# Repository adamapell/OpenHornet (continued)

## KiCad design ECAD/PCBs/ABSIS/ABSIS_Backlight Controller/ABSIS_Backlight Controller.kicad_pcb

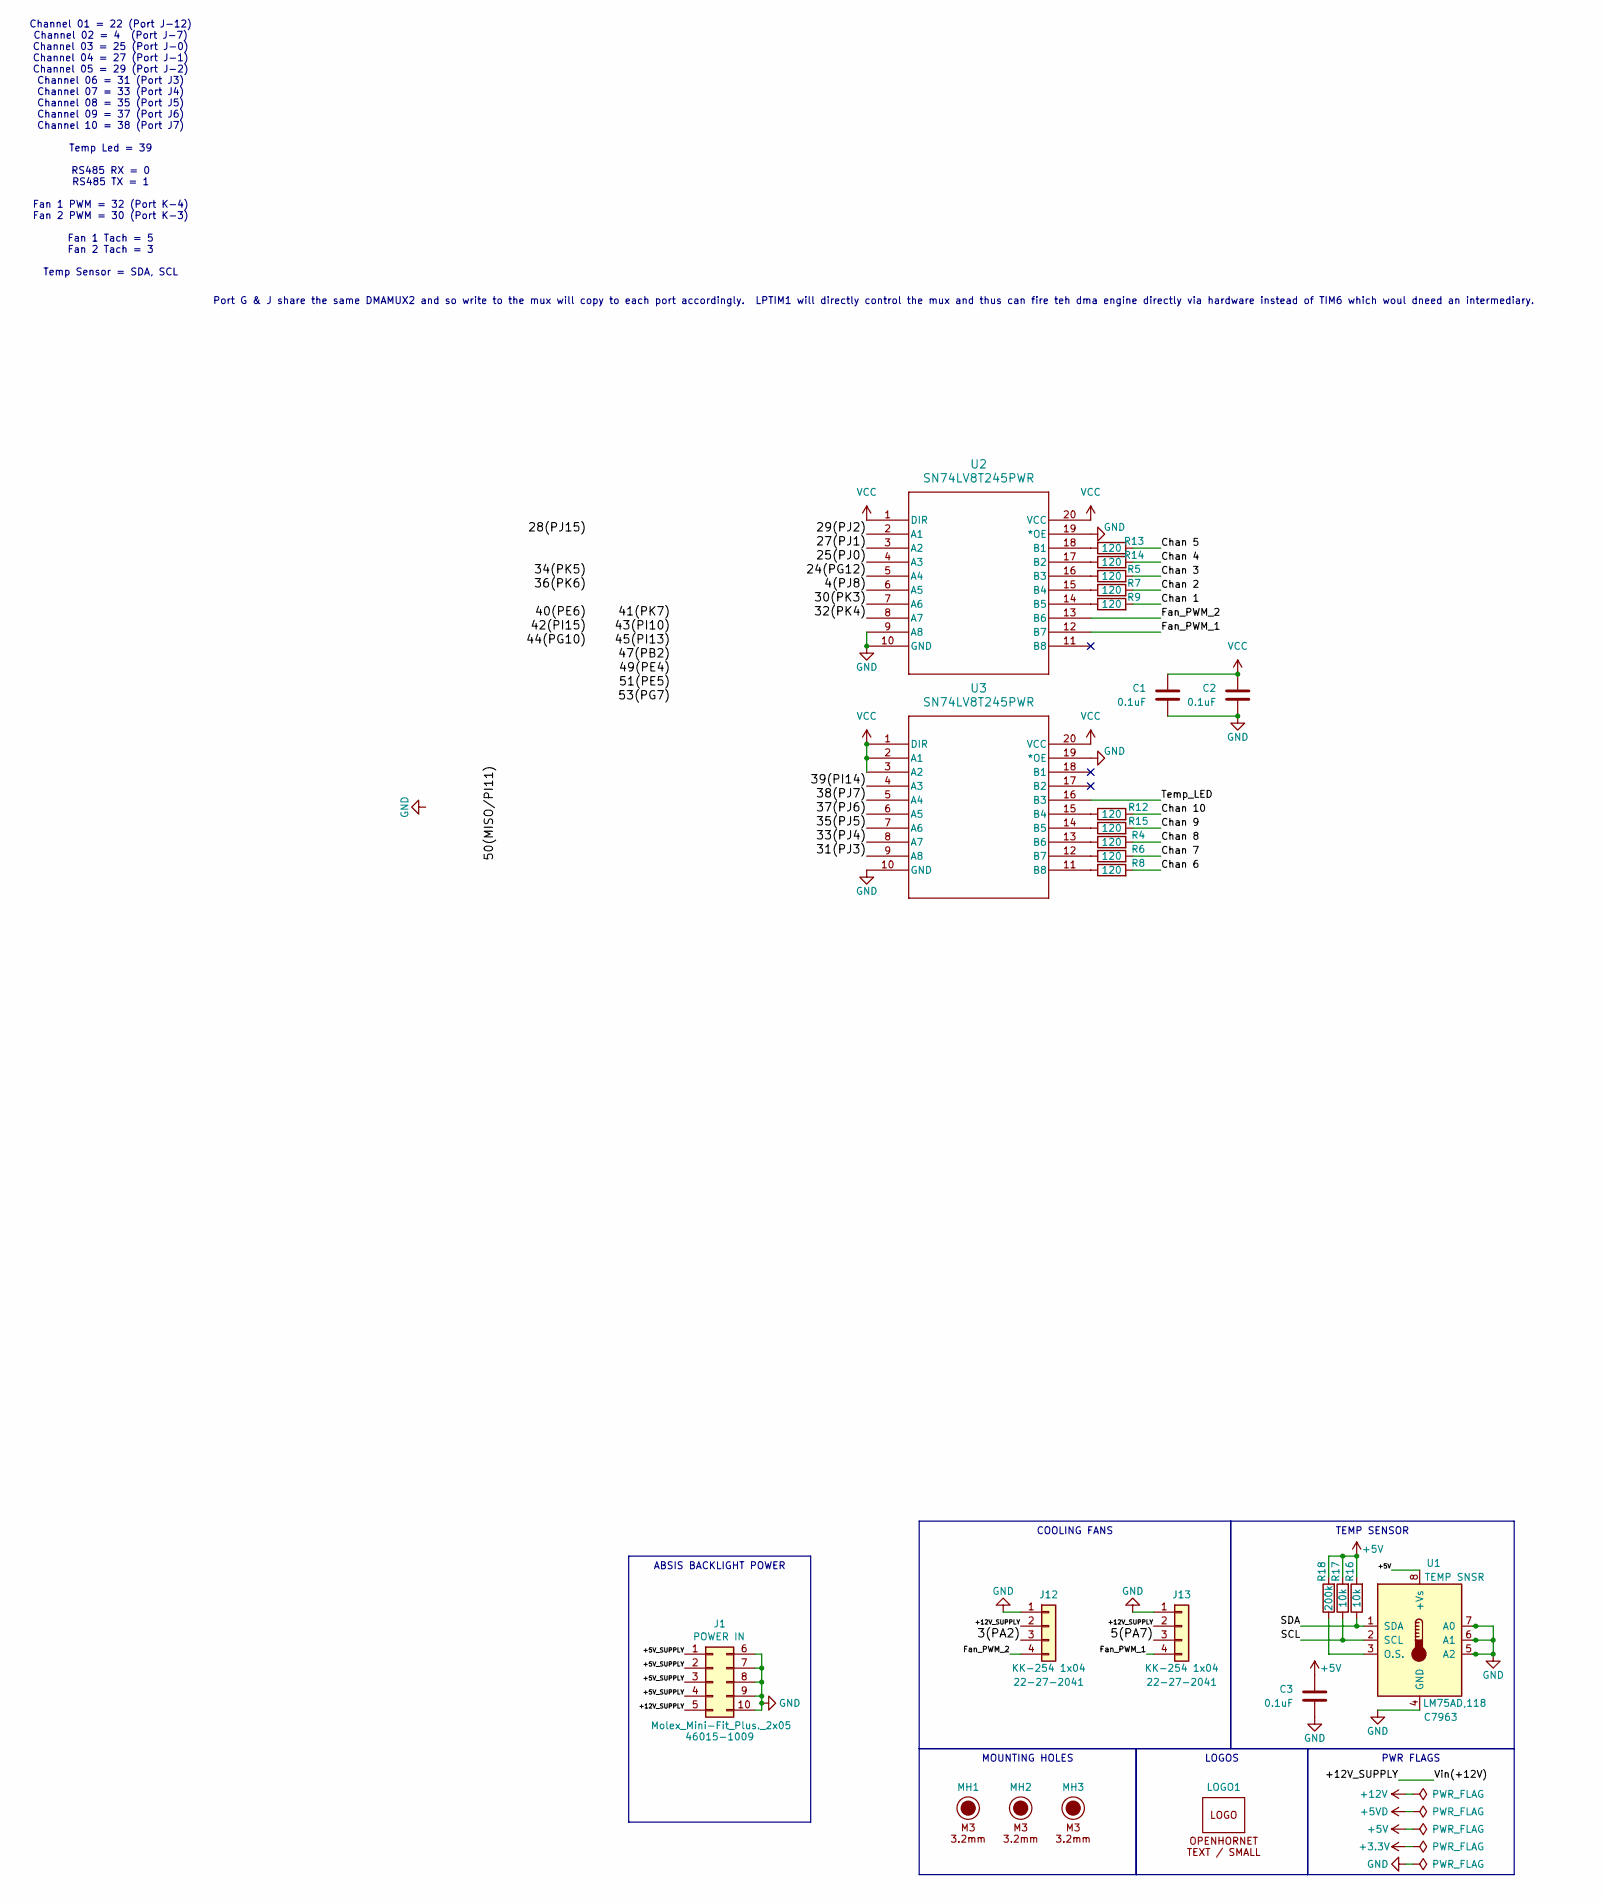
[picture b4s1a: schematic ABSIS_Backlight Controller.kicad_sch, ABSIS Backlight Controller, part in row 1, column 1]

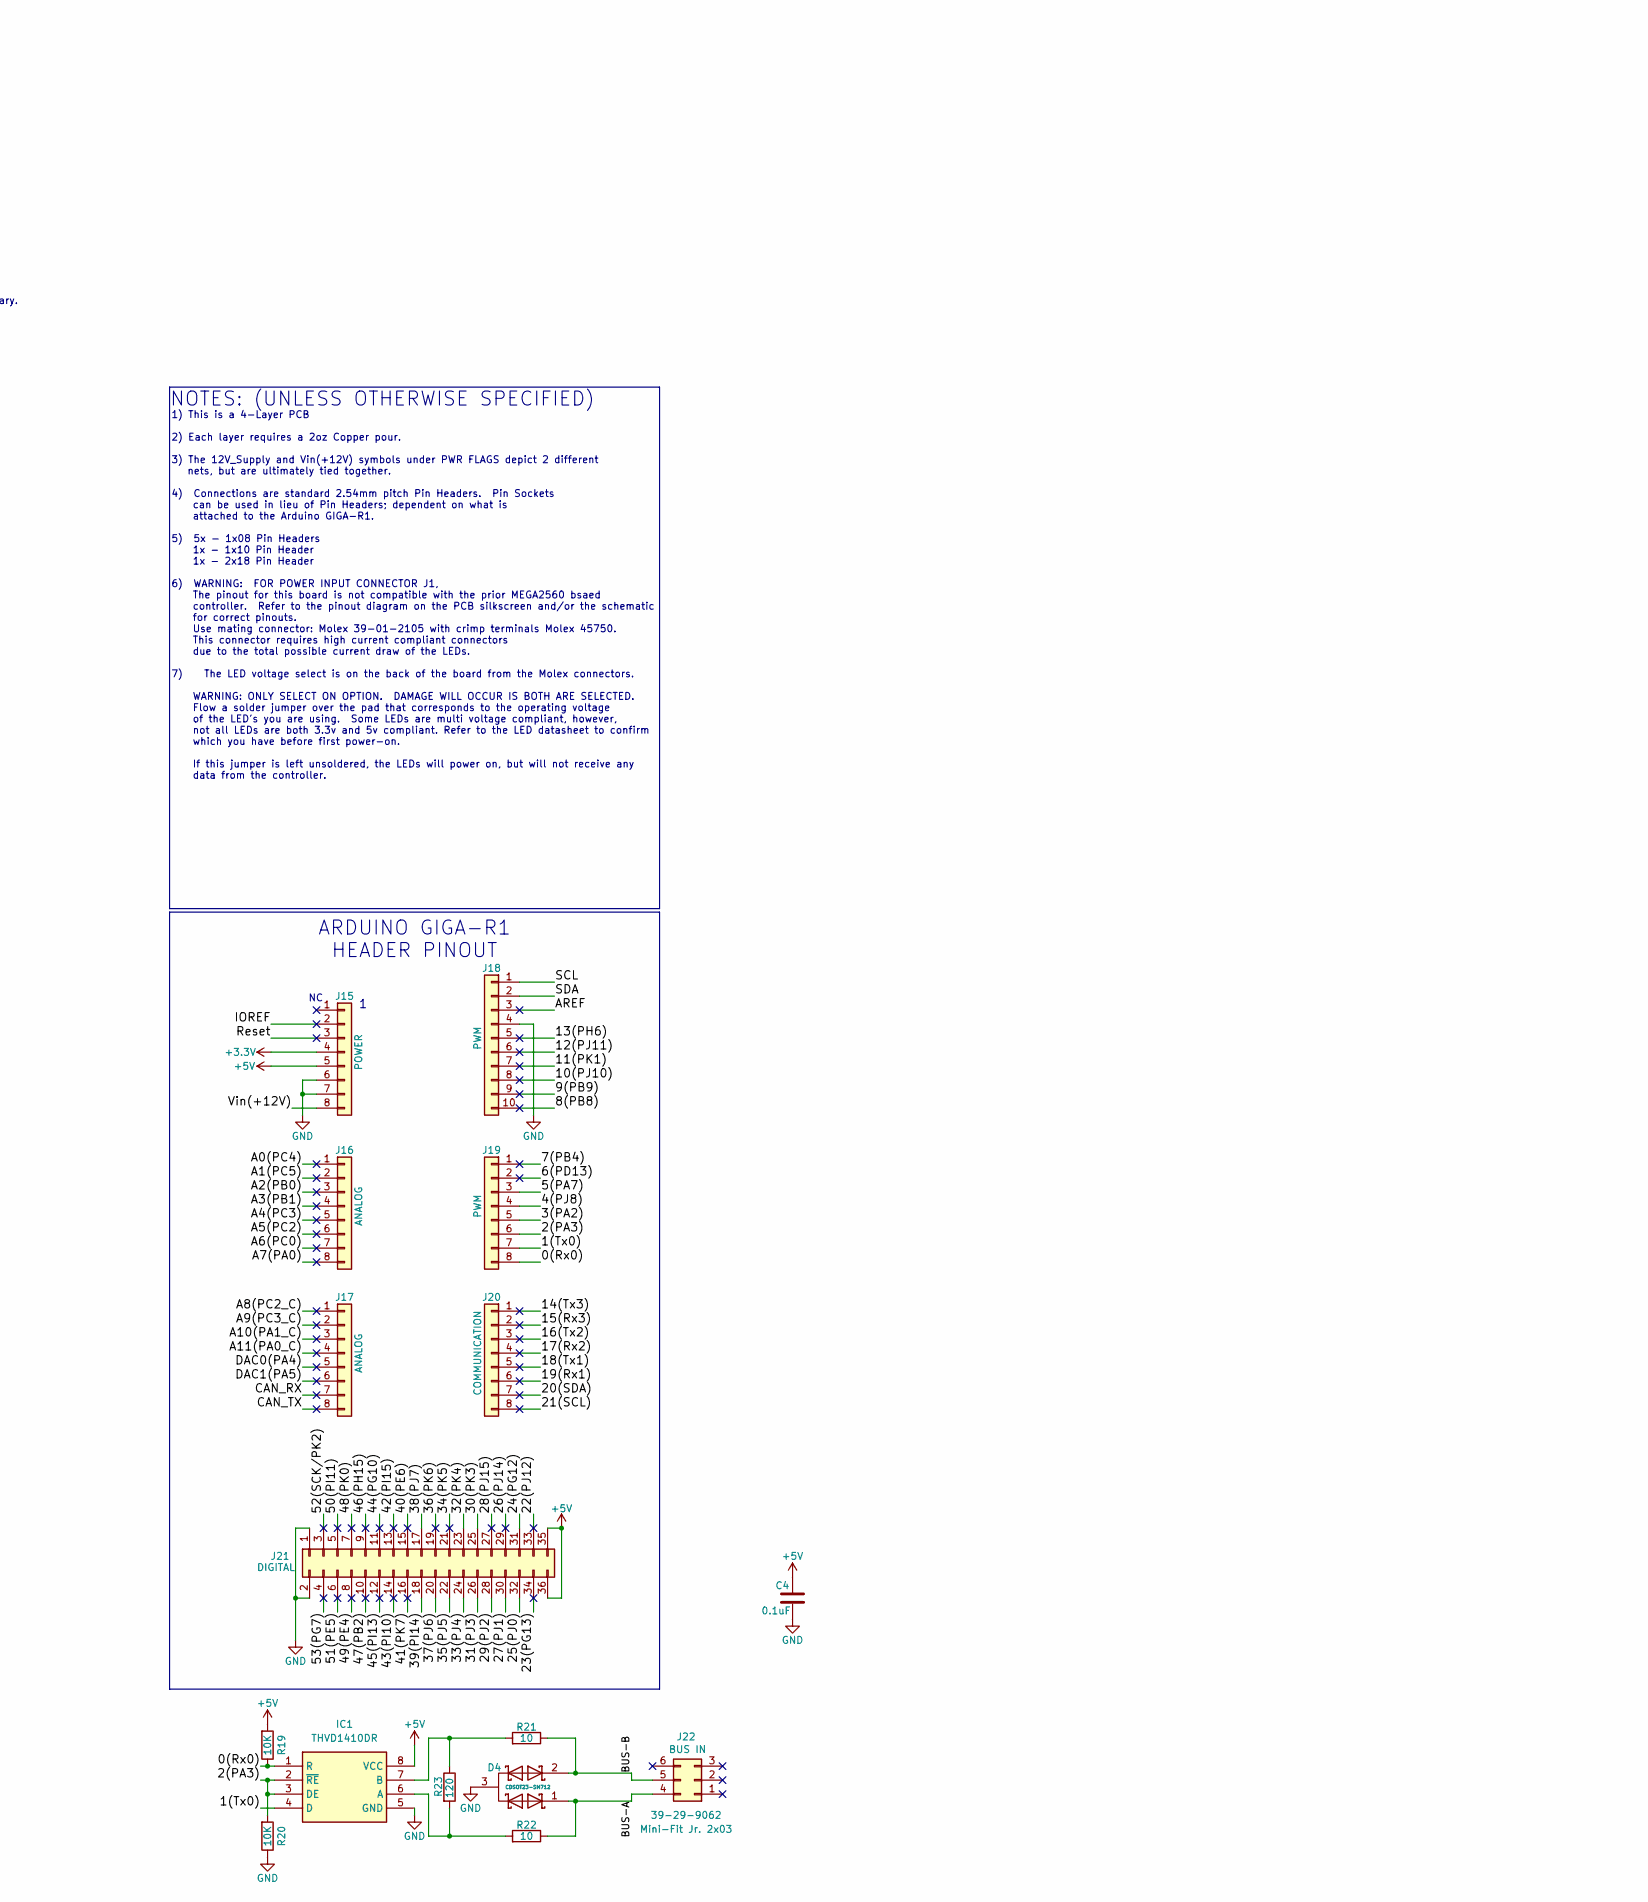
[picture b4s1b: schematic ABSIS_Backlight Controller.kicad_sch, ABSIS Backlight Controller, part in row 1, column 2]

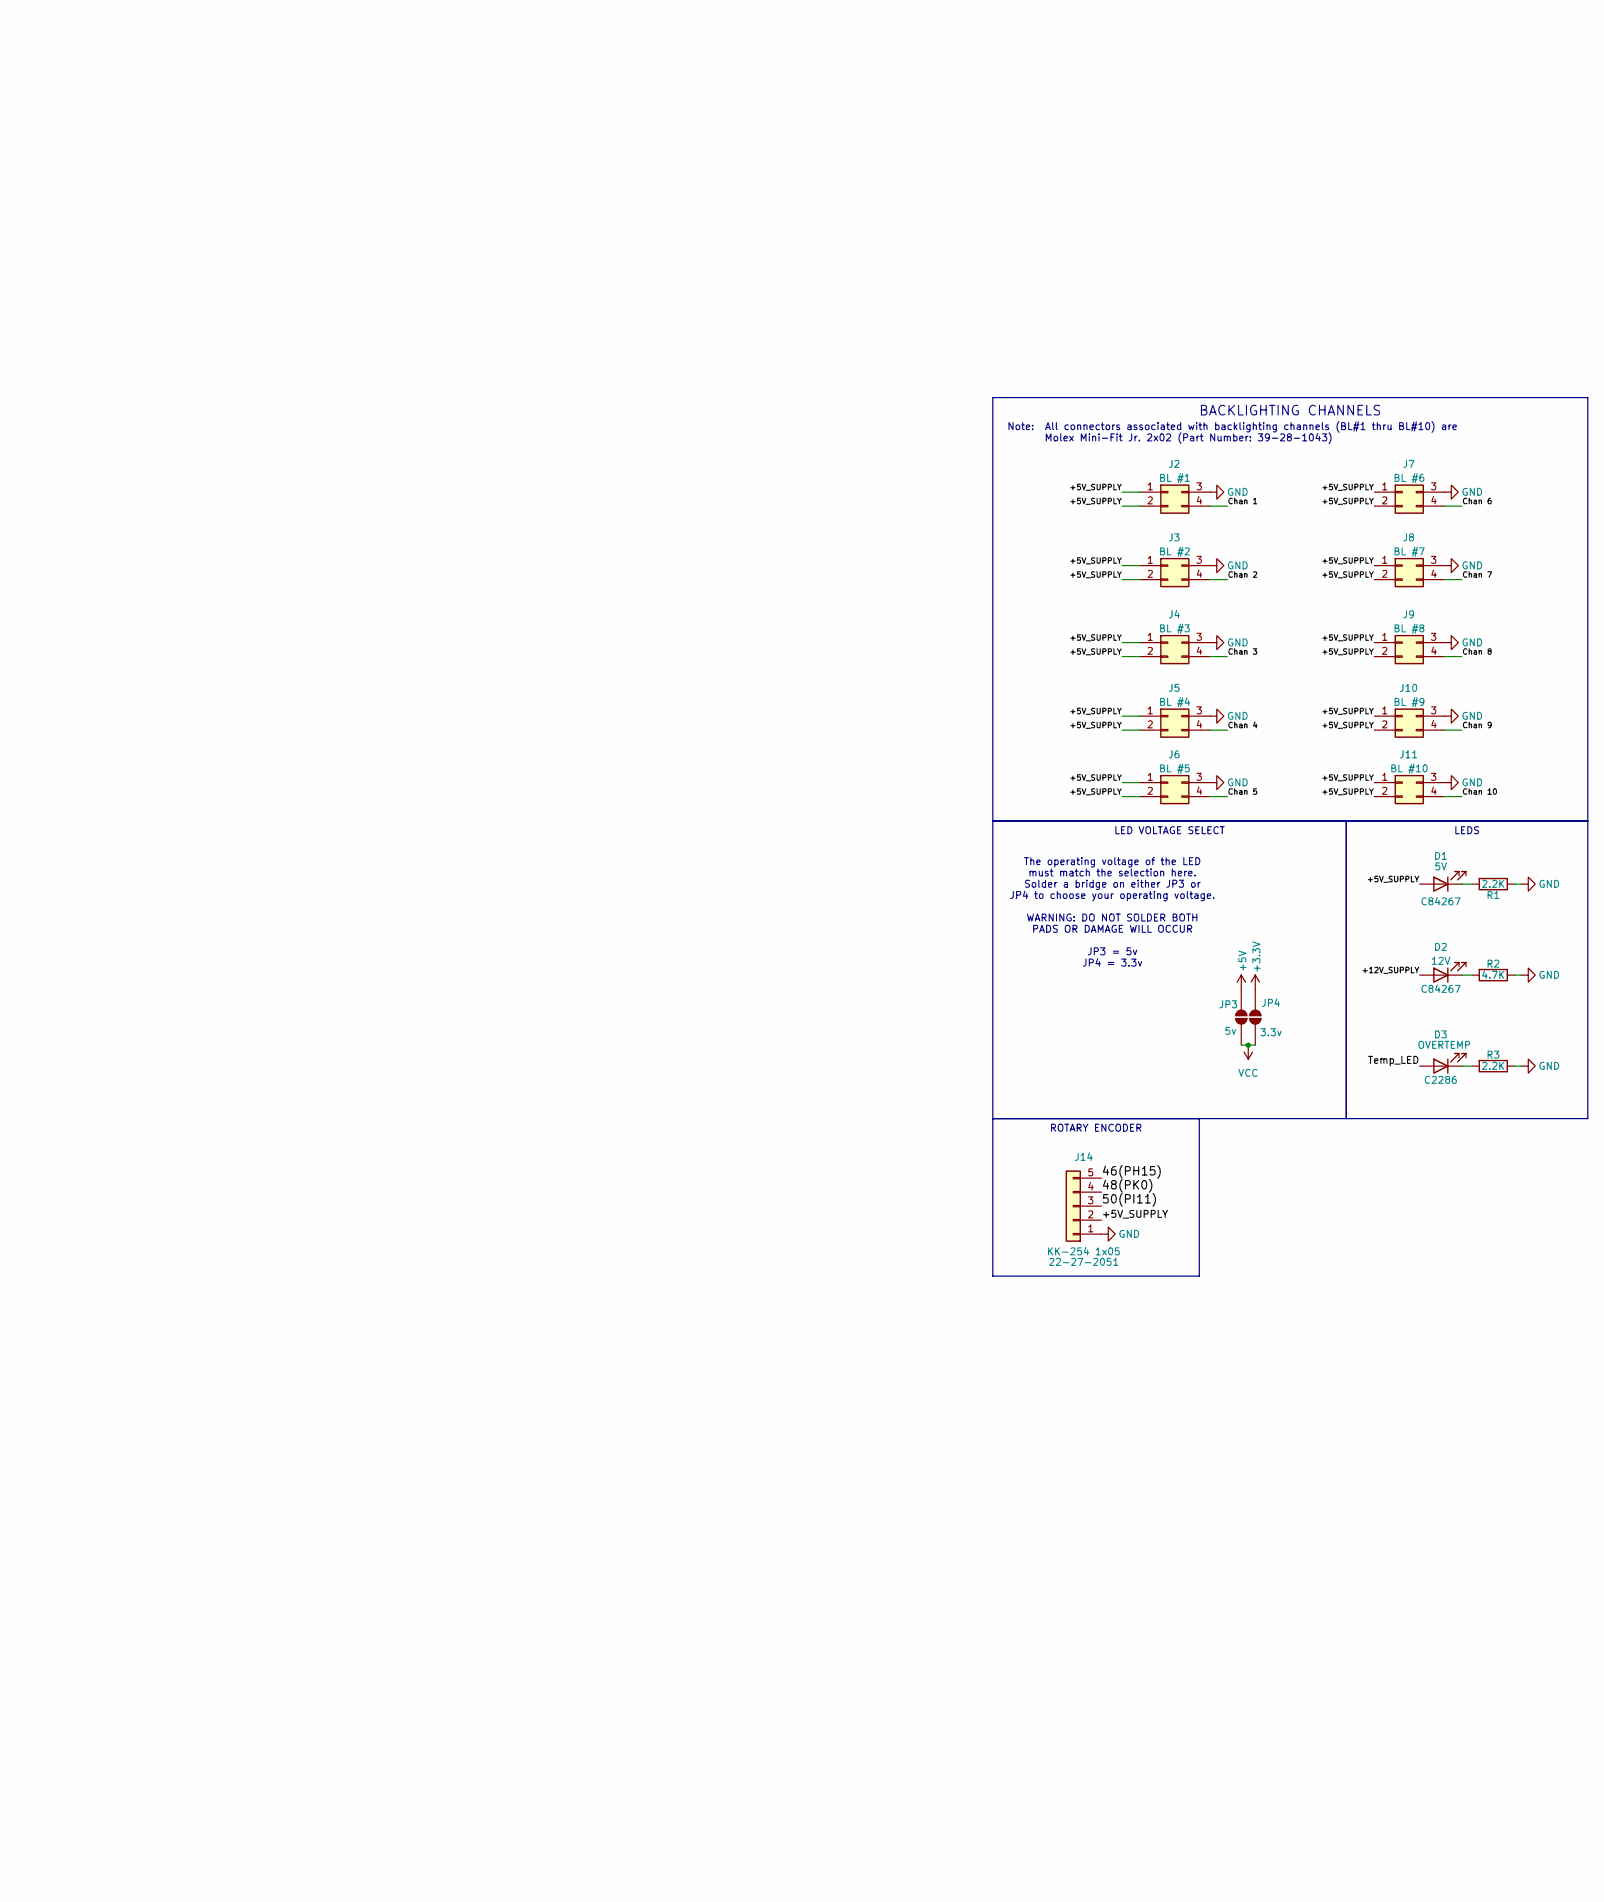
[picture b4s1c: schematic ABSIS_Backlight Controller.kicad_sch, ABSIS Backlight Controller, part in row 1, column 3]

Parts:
C1, C2, C3, C4: 0.1uF; C_0603_1608Metric; Manufacturer PN CC0603KRX7R9BB104; LCSC C14663
D1, D2: Green; LED_0603_1608Metric_Pad1.05x0.95mm_HandSolder; Manufacturer PN NCD0603G1; LCSC C84267
D3: Red; LED_0603_1608Metric_Pad1.05x0.95mm_HandSolder; Manufacturer PN KT-0603R; LCSC C2286
D4: CDSOT23-SM712; Manufacturer_Part_Number CDSOT23-SM712; Mouser Part Number 652-CDSOT23-SM712
IC1: THVD1410DR; Manufacturer_Part_Number THVD1410DR; Mouser Part Number 595-THVD1410DR
J1: Molex_Mini-Fit_Plus._2x05; Molex_Mini-Fit_Jr_5566-10A2_2x05_P4.20mm_Vertical; Manufacturer PN 46015-1009; LCSC C587474
J2, J3, J4, J5, J6, J7, J8, J9, J10, J11: Mini-Fit Jr. 2x02; Molex_Mini-Fit_Jr_5566-04A_2x02_P4.20mm_Vertical; Manufacturer PN 39-28-1043; LCSC C293502
J12, J13: KK-254 1x04; Molex_KK-254_AE-6410-04A_1x04_P2.54mm_Vertical; Manufacturer PN 22-27-2041; LCSC C504991
J14: KK-254 1x05; Molex_KK-254_AE-6410-05A_1x05_P2.54mm_Vertical; Manufacturer PN 22-27-2051; LCSC C585785
J15, J16, J17, J19, J20: PinHeader_1x08; PinHeader_1x08_P2.54mm_Vertical; Manufacturer PN PH1-08-UA
J18: PinHeader_1x10; PinHeader_1x10_P2.54mm_Vertical; Manufacturer PN PH1-10-UA
J21: PinHeader_2x18; PinHeader_2x18_P2.54mm_Vertical; Manufacturer PN PH2-18-UA
J22: Mini-Fit Jr. 2x03; Molex_Mini-Fit_Jr_5566-06A2_2x03_P4.20mm_Vertical; Manufacturer PN 39-29-9062; LCSC C505177
JP3: 5v; SolderJumper-2_P1.3mm_Open_RoundedPad1.0x1.5mm
JP4: 3.3v; SolderJumper-2_P1.3mm_Open_RoundedPad1.0x1.5mm
LOGO1: LOGO; LOGO_OH_Text_Small
MH1, MH2, MH3: M3 / 3.2mm; MountingHole_3.2mm_M3_DIN965
R1, R3: 2.2K; R_0603_1608Metric; Manufacturer PN 0603WAF2201T5E; LCSC C4190
R2: 4.7K; R_0603_1608Metric; Manufacturer PN 0603WAF4701T5E; LCSC C23162
R4, R5, R6, R7, R8, R9, R12, R13, R14, R15, R23: 120; R_0603_1608Metric; Manufacturer PN 0603WAF1200T5E; LCSC C22787
R16, R17: 10k; R_0603_1608Metric; Manufacturer PN 0603WAF1002T5E; LCSC C25804
R18: 200k; R_0603_1608Metric; Manufacturer PN 0603WAF2201T5E; LCSC C25811
R19, R20: 10K; R_0603_1608Metric_Pad0.98x0.95mm_HandSolder; LCSC C25804
R21, R22: 10; R_0603_1608Metric_Pad0.98x0.95mm_HandSolder; LCSC C844519
U1: LM75AD,118; SOIC-8_3.9x4.9mm_P1.27mm; Manufacturer PN LM75AD,118; LCSC C7963
U2, U3: SN74LV8T245PWR; TSSOP20_PW_TEX; LCSC C20345798

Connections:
+3.3V: J15.4, JP4.2 (B)
+5V: C3.1, C4.2, IC1.8 (VCC), J15.5, J21.35, J21.36, JP3.2 (B), R16.2, R17.2, R18.2, R19.2, U1.8 (+Vs)
/0(Rx0): IC1.1 (R), J19.8, R19.1
/1(Tx0): IC1.4 (D), J19.7
/2(PA3): IC1.2 (~RE), IC1.3 (DE), J19.6, R20.2
/3(PA2): J12.3, J19.5
/4(PJ8): J19.4, U2.6 (A5)
/5(PA7): J13.3, J19.3
/6(PD13): J19.2
/7(PB4): J19.1
/8(PB8): J18.10
/9(PB9): J18.9
/10(PJ10): J18.8
/11(PK1): J18.7
/12(PJ11): J18.6
/13(PH6): J18.5
/14(Tx3): J20.1
/15(Rx3): J20.2
/16(Tx2): J20.3
/17(Rx2): J20.4
/18(Tx1): J20.5
/19(Rx1): J20.6
/20(SDA): J20.7
/21(SCL): J20.8
/22(PJ12): J21.33
/23(PG13): J21.34
/24(PG12): J21.31, U2.5 (A4)
/25(PJ0): J21.32, U2.4 (A3)
/26(PJ14): J21.29
/27(PJ1): J21.30, U2.3 (A2)
/28(PJ15): J21.27
/29(PJ2): J21.28, U2.2 (A1)
/30(PK3): J21.25, U2.7 (A6)
/31(PJ3): J21.26, U3.9 (A8)
/32(PK4): J21.23, U2.8 (A7)
/33(PJ4): J21.24, U3.8 (A7)
/34(PK5): J21.21
/35(PJ5): J21.22, U3.7 (A6)
/36(PK6): J21.19
/37(PJ6): J21.20, U3.6 (A5)
/38(PJ7): J21.17, U3.5 (A4)
/39(PI14): J21.18, U3.4 (A3)
/40(PE6): J21.15
/41(PK7): J21.16
/42(PI15): J21.13
/43(PI10): J21.14
/44(PG10): J21.11
/45(PI13): J21.12
/46(PH15): J14.5, J21.9
/47(PB2): J21.10
/48(PK0): J14.4, J21.7
/49(PE4): J21.8
/50(PI11): J14.3, J21.5
/51(PE5): J21.6
/52(SCK/PK2): J21.3
/53(PG7): J21.4
/+5V_SUPPLY: D1.2 (A), J1.1, J1.2, J1.3, J1.4, J2.1, J2.2 (Pin_3), J3.1, J3.2 (Pin_3), J4.1, J4.2 (Pin_3), J5.1, J5.2 (Pin_3), J6.1, J6.2 (Pin_3), J7.1, J7.2 (Pin_3), J8.1, J8.2 (Pin_3), J9.1, J9.2 (Pin_3), J10.1, J10.2 (Pin_3), J11.1, J11.2 (Pin_3), J14.2
/+12V_SUPPLY: D2.2 (A), J1.5, J12.2, J13.2, J15.8
/A0(PC4): J16.1
/A1(PC5): J16.2
/A2(PB0): J16.3
/A3(PB1): J16.4
/A4(PC3): J16.5
/A5(PC2): J16.6
/A6(PC0): J16.7
/A7(PA0): J16.8
/A8(PC2_C): J17.1
/A9(PC3_C): J17.2
/A10(PA1_C): J17.3
/A11(PA0_C): J17.4
/AREF: J18.3
/BUS-A: D4.1, J22.4, R22.2
/BUS-B: D4.2, J22.5, R21.2
/CAN_RX: J17.7
/CAN_TX: J17.8
/Chan 1: J2.4, R9.2
/Chan 2: J3.4, R7.2
/Chan 3: J4.4, R5.2
/Chan 4: J5.4, R14.2
/Chan 5: J6.4, R13.2
/Chan 6: J7.4, R8.2
/Chan 7: J8.4, R6.2
/Chan 8: J9.4, R4.2
/Chan 9: J10.4, R15.2
/Chan 10: J11.4, R12.2
/DAC0(PA4): J17.5
/DAC1(PA5): J17.6
/Fan_PWM_1: J13.4, U2.12 (B7)
/Fan_PWM_2: J12.4, U2.13 (B6)
/IOREF: J15.2
/Reset: J15.3
/SCL: J18.1, R17.1, U1.2 (SCL)
/SDA: J18.2, R16.1, U1.1 (SDA)
/Temp_LED: D3.2 (A), U3.16 (B3)
GND: C1.2, C2.2, C3.2, C4.1, D4.3, IC1.5 (GND), J1.6, J1.7, J1.8, J1.9, J1.10, J2.3 (Pin_2), J3.3 (Pin_2), J4.3 (Pin_2), J5.3 (Pin_2), J6.3 (Pin_2), J7.3 (Pin_2), J8.3 (Pin_2), J9.3 (Pin_2), J10.3 (Pin_2), J11.3 (Pin_2), J12.1, J13.1, J14.1, J15.6, J15.7, J18.4, J21.1, J21.2, R1.1, R2.1, R3.1, R20.1, U1.4 (GND), U1.5 (A2), U1.6 (A1), U1.7 (A0), U2.9 (A8), U2.10 (GND), U2.19 (*OE), U3.10 (GND), U3.19 (*OE)
unnamed: D1.1 (K), R1.2
unnamed: D2.1 (K), R2.2
unnamed: D3.1 (K), R3.2
unnamed: IC1.6 (A), R22.1, R23.1
unnamed: IC1.7 (B), R21.1, R23.2
unnamed: R18.1, U1.3 (O.S.)
unnamed: R13.1, U2.18 (B1)
unnamed: R14.1, U2.17 (B2)
unnamed: R5.1, U2.16 (B3)
unnamed: R7.1, U2.15 (B4)
unnamed: R9.1, U2.14 (B5)
unnamed: R12.1, U3.15 (B4)
unnamed: R15.1, U3.14 (B5)
unnamed: R4.1, U3.13 (B6)
unnamed: R6.1, U3.12 (B7)
unnamed: R8.1, U3.11 (B8)
VCC: C1.1, C2.1, JP3.1 (A), JP4.1 (A), U2.1 (DIR), U2.20 (VCC), U3.1 (DIR), U3.2 (A1), U3.3 (A2), U3.20 (VCC)

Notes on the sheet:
The operating voltage of the LED must match the selection here. Solder a bridge on either JP3 or JP4 to choose your operating voltage. WARNING: DO NOT SOLDER BOTH PADS OR DAMAGE WILL OCCUR JP3 = 5v JP4 = 3.3v
1) This is a 4-Layer PCB 2) Each layer requires a 2oz Copper pour. 3) The 12V_Supply and Vin(+12V) symbols under PWR FLAGS depict 2 different nets, but are ultimately tied together. 4) Connections are standard 2.54mm pitch Pin Headers. Pin Sockets can be used in lieu of Pin Headers; dependent on wh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
Port G & J share the same DMAMUX2 and so write to the mux will copy to each port accordingly. LPTIM1 will directly control the mux and thus can fire teh dma engine directly via hardware instead of TIM6 which woul dneed an intermediary.
Note: All connectors associated with backlighting channels (BL#1 thru BL#10) are Molex Mini-Fit Jr. 2x02 (Part Number: 39-28-1043)
Channel 01 = 22 (Port J-12) Channel 02 = 4 (Port J-7) Channel 03 = 25 (Port J-0) Channel 04 = 27 (Port J-1) Channel 05 = 29 (Port J-2) Channel 06 = 31 (Port J3) Channel 07 = 33 (Port J4) Channel 08 = 35 (Port J5) Channel 09 = 37 (Port J6) Channel 10 = 38 (Port J7) Temp Led = 39 RS485 RX = 0 RS485 T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
NOTES: (UNLESS OTHERWISE SPECIFIED)
LEDS
BACKLIGHTING CHANNELS
ABSIS BACKLIGHT POWER
ROTARY ENCODER
TEMP SENSOR
PWR FLAGS
COOLING FANS
LOGOS
MOUNTING HOLES
ARDUINO GIGA-R1 HEADER PINOUT
LED VOLTAGE SELECT

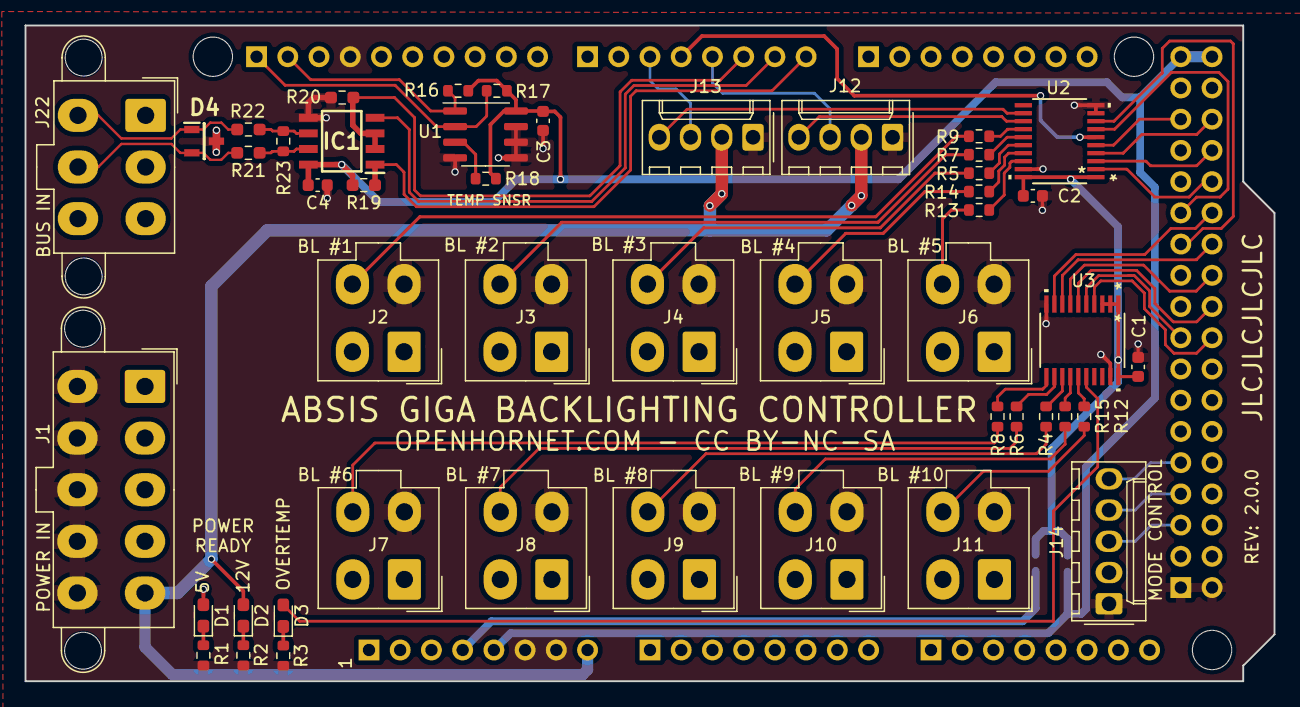
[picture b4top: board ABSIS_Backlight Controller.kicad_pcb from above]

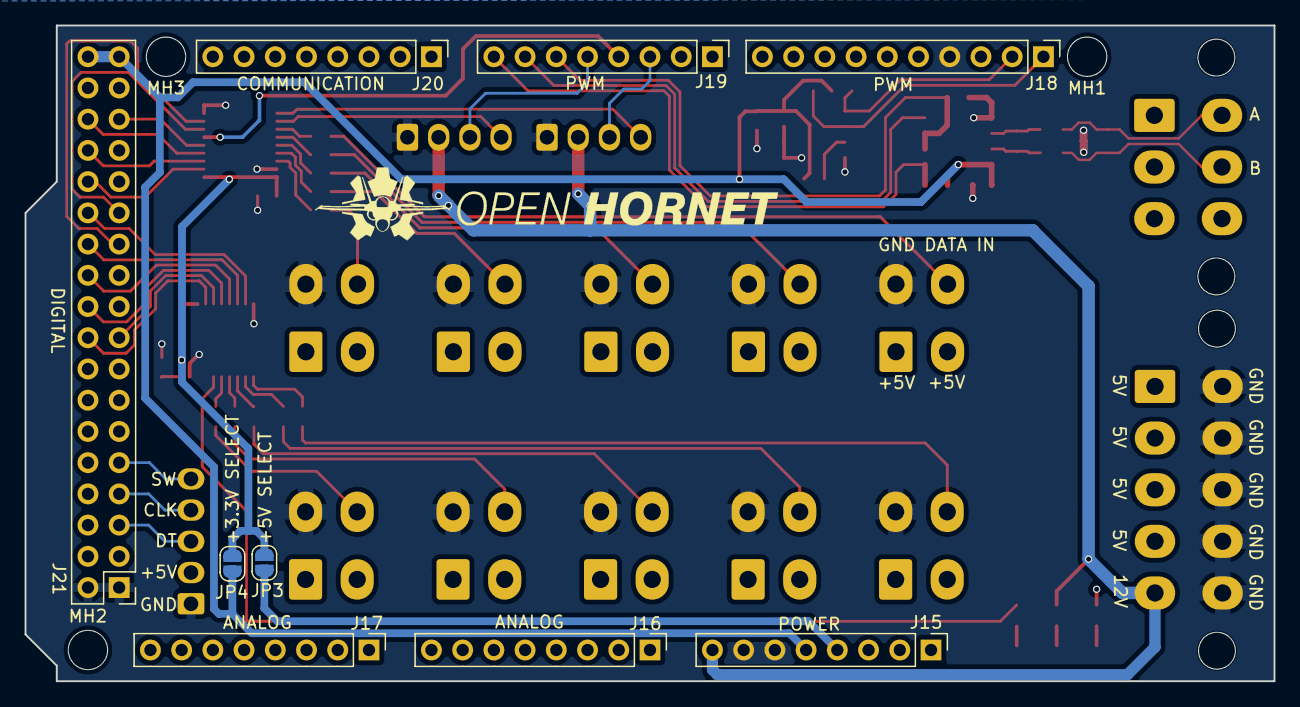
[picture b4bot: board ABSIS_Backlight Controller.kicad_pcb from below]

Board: 4 copper layers, 101.6 x 53.3 mm, 61 parts (13 on the bottom side), 60 nets.

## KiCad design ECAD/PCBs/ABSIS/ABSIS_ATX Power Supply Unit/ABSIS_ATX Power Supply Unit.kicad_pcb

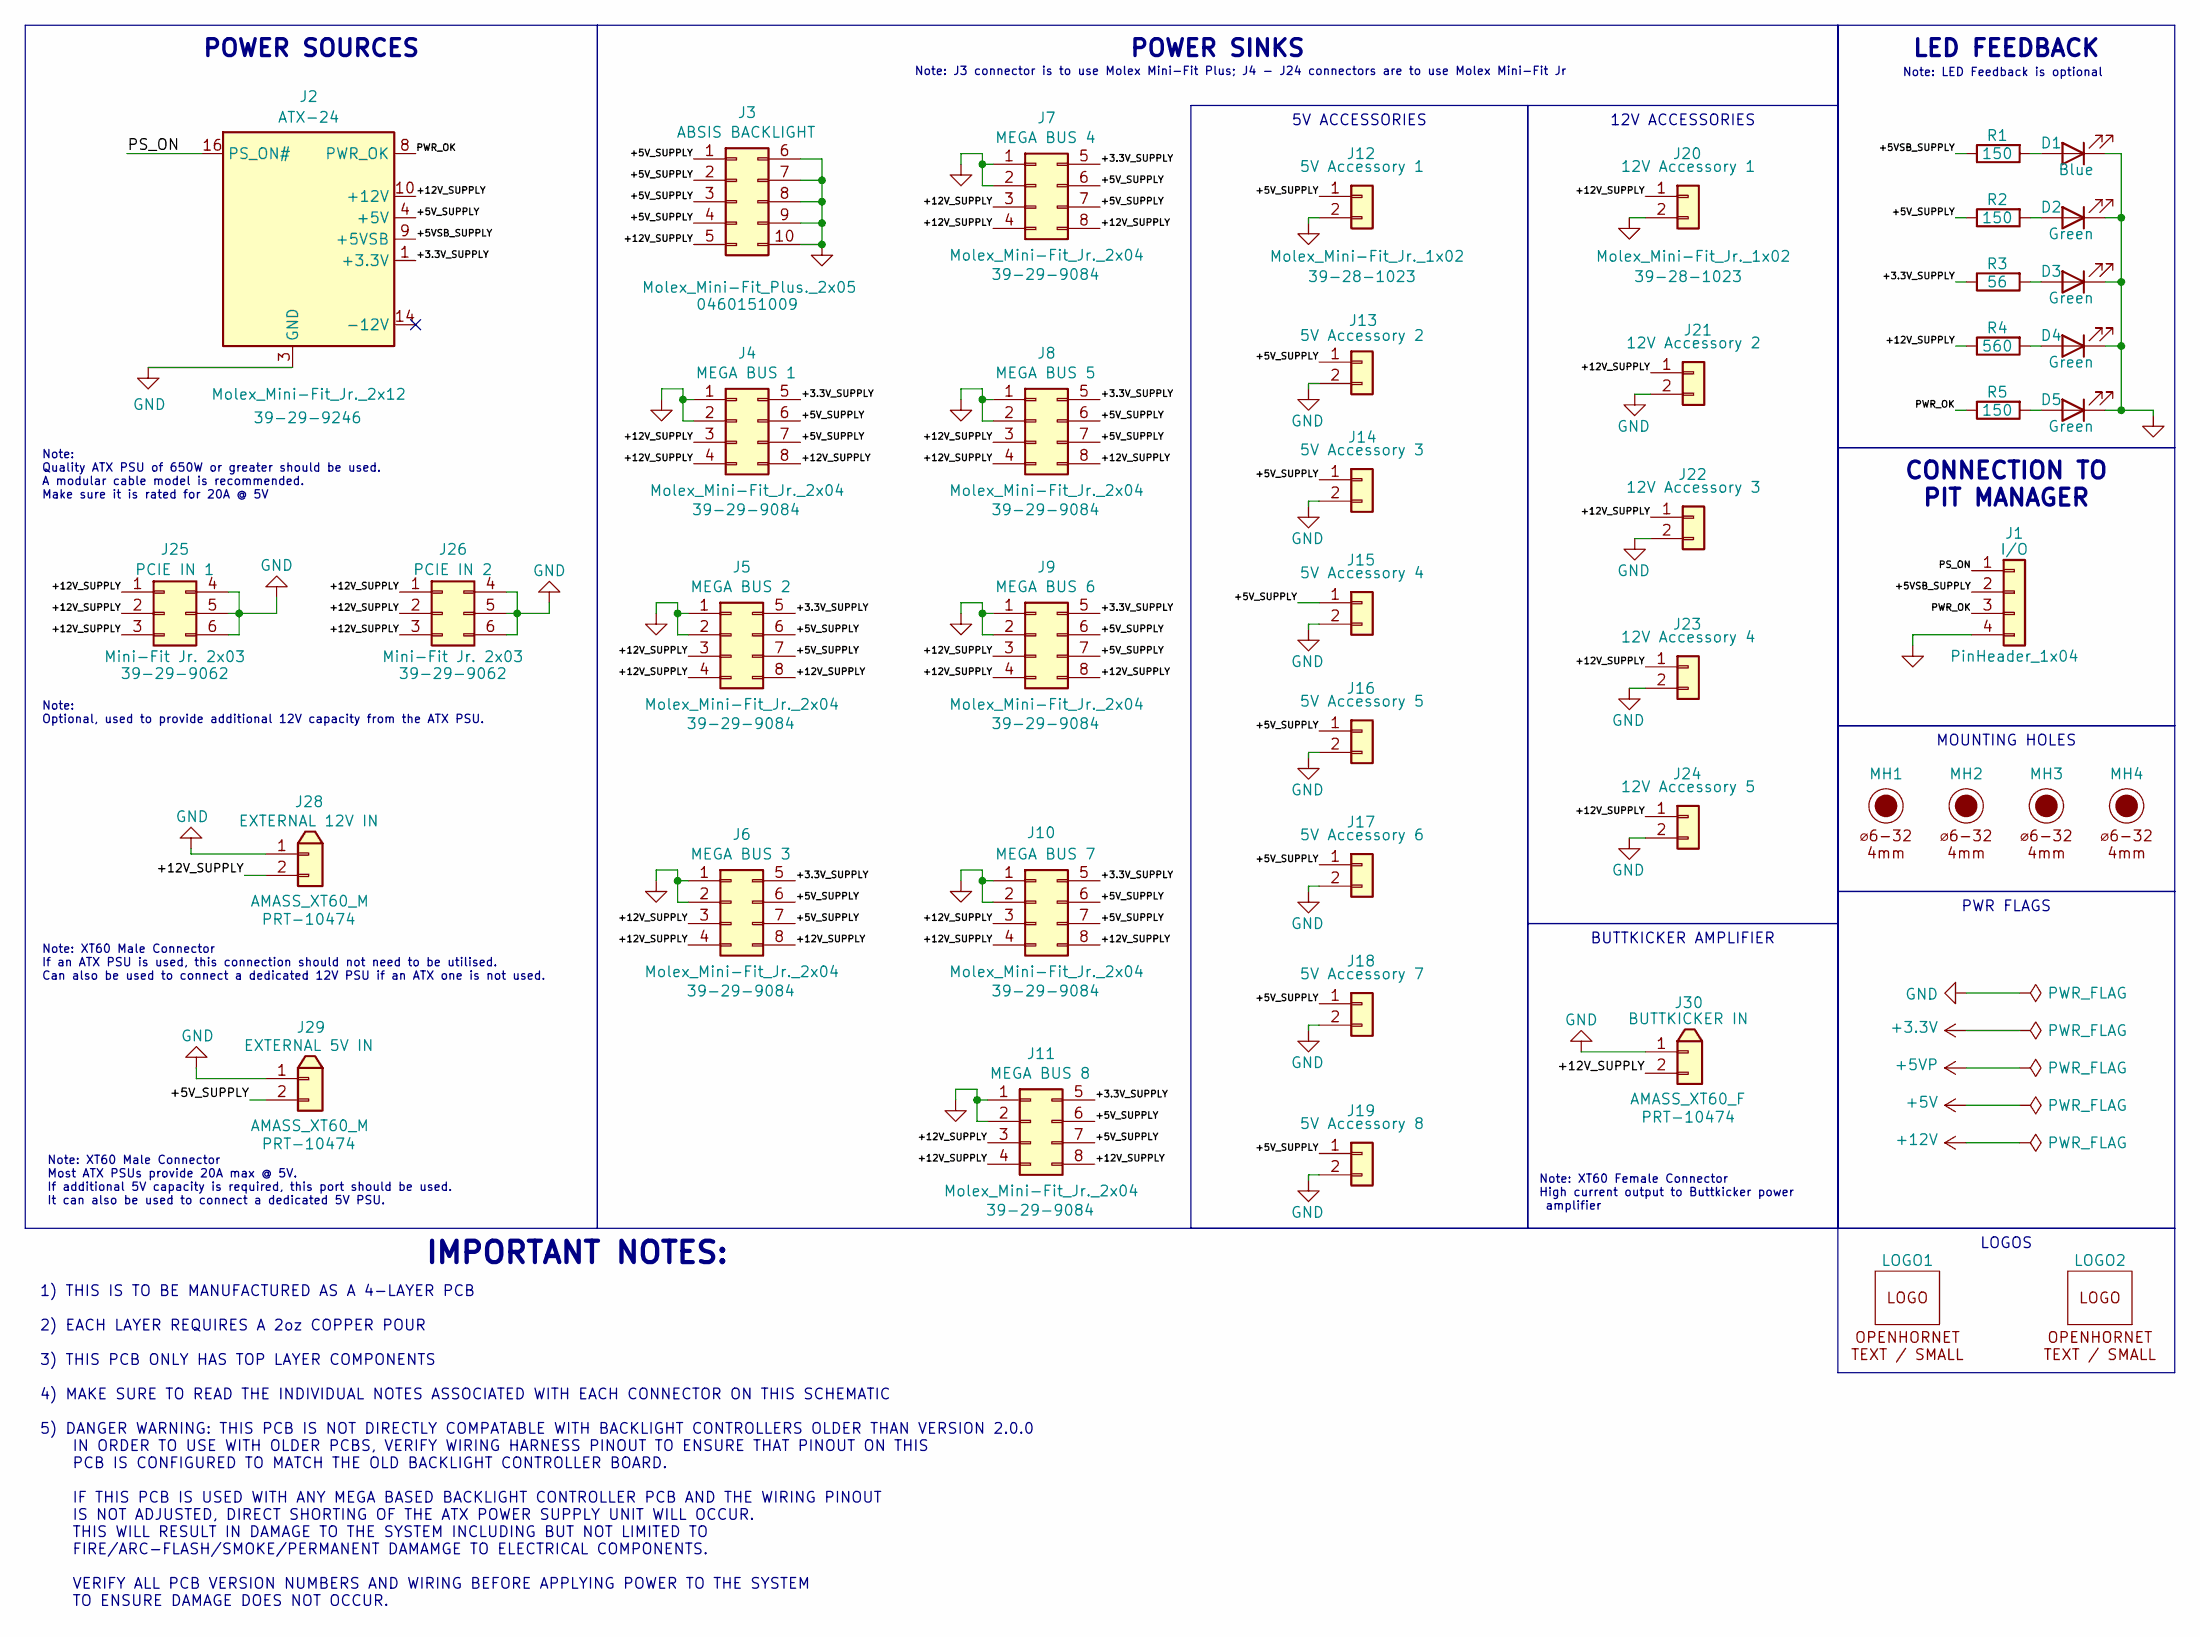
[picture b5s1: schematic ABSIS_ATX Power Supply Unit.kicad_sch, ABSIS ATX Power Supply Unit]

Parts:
D1: Blue; LED_D3.0mm; Manufacturer PN 151033BS03000
D2, D3, D4, D5: Green; LED_D3.0mm; Manufacturer PN 151031VS06000
J1: PinHeader_1x04; PinHeader_1x04_P2.54mm_Vertical
J2: Molex_Mini-Fit_Jr._2x12; Molex_Mini-Fit_Jr_5566-24A2_2x12_P4.20mm_Vertical; Manufacturer PN 39-29-9246; LCSC C587483
J3: Molex_Mini-Fit_Plus._2x05; Molex_Mini-Fit_Jr_5566-10A2_2x05_P4.20mm_Vertical; Manufacturer PN 0460151009; LCSC C17600683
J4, J5, J6, J7, J8, J9, J10, J11: Molex_Mini-Fit_Jr._2x04; Molex_Mini-Fit_Jr_5566-08A2_2x04_P4.20mm_Vertical; Manufacturer PN 39-29-9084; LCSC C587470
J12, J13, J14, J15, J16, J17, J18, J19, J20, J21, J22, J23, J24: Molex_Mini-Fit_Jr._1x02; Molex_Mini-Fit_Jr_5566-02A_2x01_P4.20mm_Vertical; Manufacturer PN 39-28-1023; LCSC C234186
J25, J26: Mini-Fit Jr. 2x03; Molex_Mini-Fit_Jr_5566-06A_2x03_P4.20mm_Vertical; Manufacturer PN 39-29-9062; LCSC C505177
J28, J29: AMASS_XT60_M; AMASS_XT60-M_1x02_P7.20mm_Vertical; Manufacturer PN PRT-10474; LCSC C98733
J30: AMASS_XT60_F; AMASS_XT60-F_1x02_P7.20mm_Vertical; Manufacturer PN PRT-10474; LCSC C98734
LOGO1, LOGO2: LOGO; LOGO_OH_Text_Small
MH1, MH2, MH3, MH4: 6x32 / 4mm; MountingHole_6-32_PHS
R1, R2, R5: 150; R_Axial_DIN0207_L6.3mm_D2.5mm_P7.62mm_Horizontal; Manufacturer PN CFR-25JB-52-150R; LCSC C1365790
R3: 56; R_Axial_DIN0207_L6.3mm_D2.5mm_P7.62mm_Horizontal; Manufacturer PN CFR-25JB-52-56R; LCSC C3357490
R4: 560; R_Axial_DIN0207_L6.3mm_D2.5mm_P7.62mm_Horizontal; Manufacturer PN CFR-25JB-52-560R; LCSC C1364372

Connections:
/+3.3V_SUPPLY: J2.1 (+3.3V), J2.2 (+3.3V), J2.12 (+3.3V), J2.13 (+3.3V), J4.5, J5.5, J6.5, J7.5, J8.5, J9.5, J10.5, J11.5, R3.2
/+5VSB_SUPPLY: J1.2, J2.9 (+5VSB), R1.2
/+5V_SUPPLY: J2.4 (+5V), J2.6 (+5V), J2.21 (+5V), J2.22 (+5V), J2.23 (+5V), J3.1, J3.2, J3.3, J3.4, J4.6, J4.7, J5.6, J5.7, J6.6, J6.7, J7.6, J7.7, J8.6, J8.7, J9.6, J9.7, J10.6, J10.7, J11.6, J11.7, J12.1, J13.1, J14.1, J15.1, J16.1, J17.1, J18.1, J19.1, J29.2, R2.2
/+12V_SUPPLY: J2.10 (+12V), J2.11 (+12V), J3.5, J4.3, J4.4, J4.8, J5.3, J5.4, J5.8, J6.3, J6.4, J6.8, J7.3, J7.4, J7.8, J8.3, J8.4, J8.8, J9.3, J9.4, J9.8, J10.3, J10.4, J10.8, J11.3, J11.4, J11.8, J20.1, J21.1, J22.1, J23.1, J24.1, J25.1, J25.2, J25.3, J26.1, J26.2, J26.3, J28.2, J30.2, R4.2
/PS_ON: J1.1, J2.16 (PS_ON#)
/PWR_OK: J1.3, J2.8 (PWR_OK), R5.2
GND: D1.1 (K), D2.1 (K), D3.1 (K), D4.1 (K), D5.1 (K), J1.4, J2.3 (GND), J2.5 (GND), J2.7 (GND), J2.15 (GND), J2.17 (GND), J2.18 (GND), J2.19 (GND), J2.24 (GND), J3.6, J3.7, J3.8, J3.9, J3.10, J4.1, J4.2, J5.1, J5.2, J6.1, J6.2, J7.1, J7.2, J8.1, J8.2, J9.1, J9.2, J10.1, J10.2, J11.1, J11.2, J12.2, J13.2, J14.2, J15.2, J16.2, J17.2, J18.2, J19.2, J20.2, J21.2, J22.2, J23.2, J24.2, J25.4, J25.5, J25.6, J26.4, J26.5, J26.6, J28.1, J29.1, J30.1
unnamed: D1.2 (A), R1.1
unnamed: D2.2 (A), R2.1
unnamed: D3.2 (A), R3.1
unnamed: D4.2 (A), R4.1
unnamed: D5.2 (A), R5.1

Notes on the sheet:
Note: LED Feedback is optional
1) THIS IS TO BE MANUFACTURED AS A 4-LAYER PCB 2) EACH LAYER REQUIRES A 2oz COPPER POUR 3) THIS PCB ONLY HAS TOP LAYER COMPONENTS 4) MAKE SURE TO READ THE INDIVIDUAL NOTES ASSOCIATED WITH EACH CONNECTOR ON THIS SCHEMATIC 5) DANGER WARNING: THIS PCB IS NOT DIRECTLY COMPATABLE WITH BACKLIGHT CONTROLL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
Note: J3 connector is to use Molex Mini-Fit Plus; J4 - J24 connectors are to use Molex Mini-Fit Jr
Note: Optional, used to provide additional 12V capacity from the ATX PSU.
Note: XT60 Male Connector If an ATX PSU is used, this connection should not need to be utilised. Can also be used to connect a dedicated 12V PSU if an ATX one is not used.
Note: Quality ATX PSU of 650W or greater should be used. A modular cable model is recommended. Make sure it is rated for 20A @ 5V
Note: XT60 Female Connector High current output to Buttkicker power amplifier
Note: XT60 Male Connector Most ATX PSUs provide 20A max @ 5V. If additional 5V capacity is required, this port should be used. It can also be used to connect a dedicated 5V PSU.
IMPORTANT NOTES:
POWER SOURCES
BUTTKICKER AMPLIFIER
CONNECTION TO PIT MANAGER
MOUNTING HOLES
LED FEEDBACK
LOGOS
5V ACCESSORIES
PWR FLAGS
POWER SINKS
12V ACCESSORIES

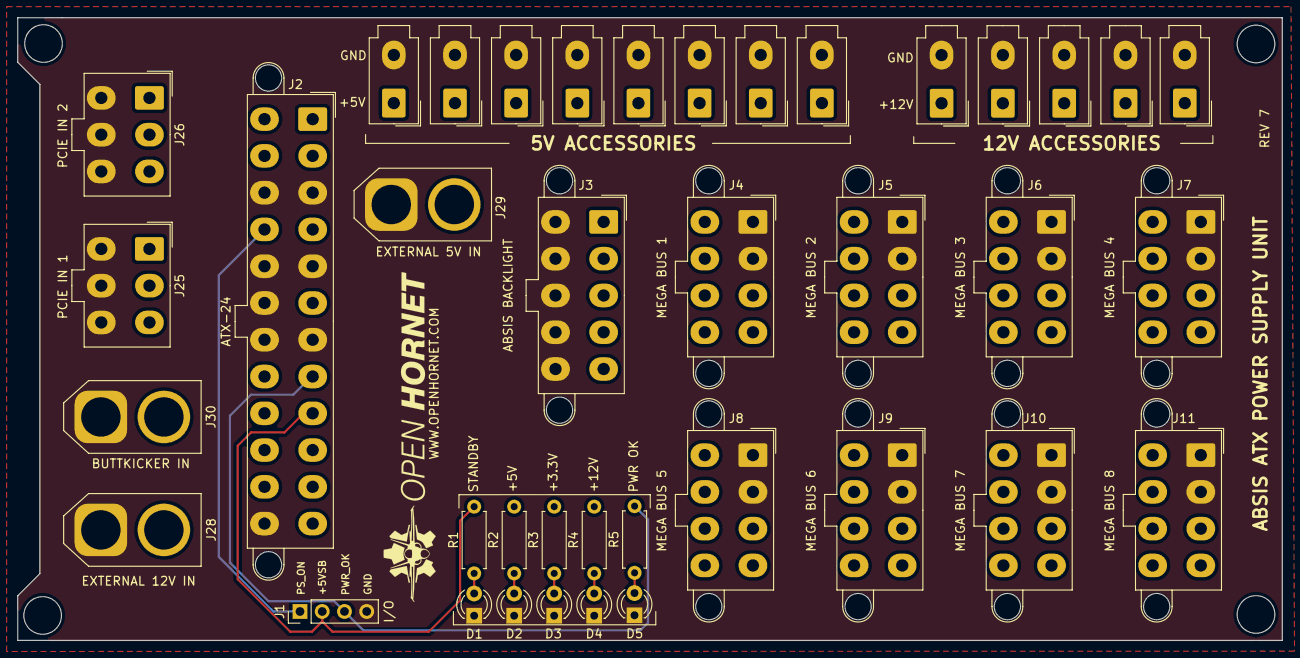
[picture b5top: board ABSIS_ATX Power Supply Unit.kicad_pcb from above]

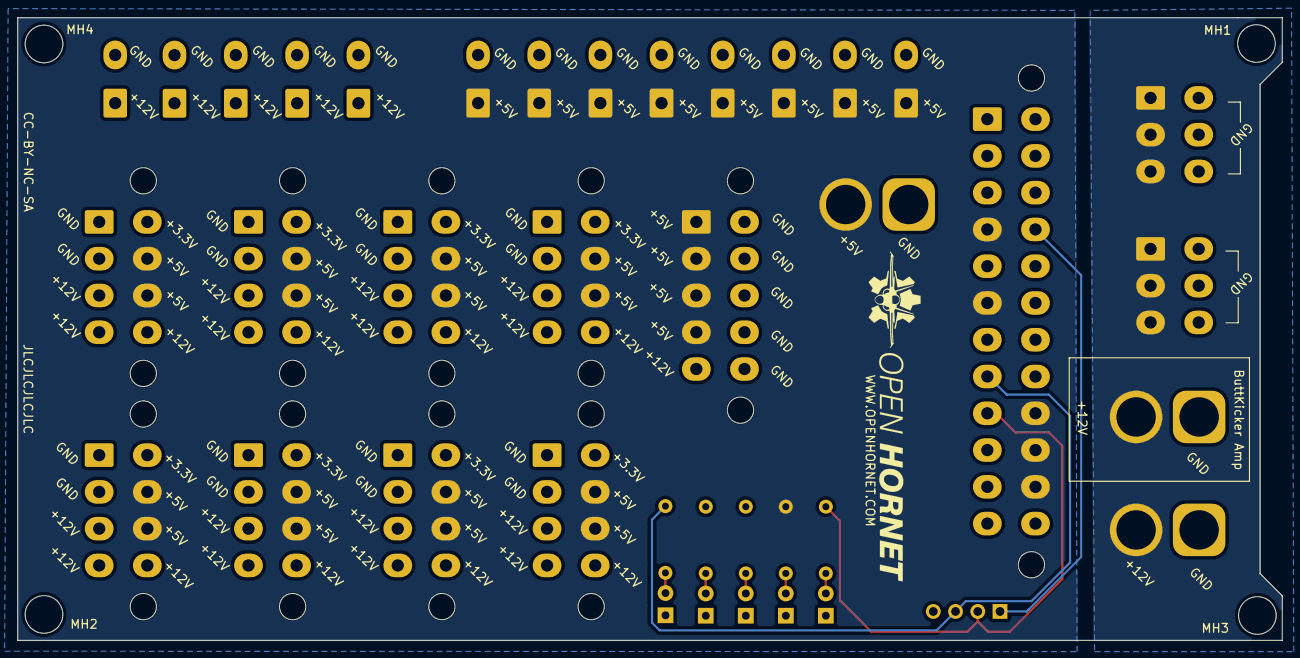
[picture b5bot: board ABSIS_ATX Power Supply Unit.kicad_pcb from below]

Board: 4 copper layers, 144.4 x 71.1 mm, 45 parts (5 on the bottom side), 12 nets.
